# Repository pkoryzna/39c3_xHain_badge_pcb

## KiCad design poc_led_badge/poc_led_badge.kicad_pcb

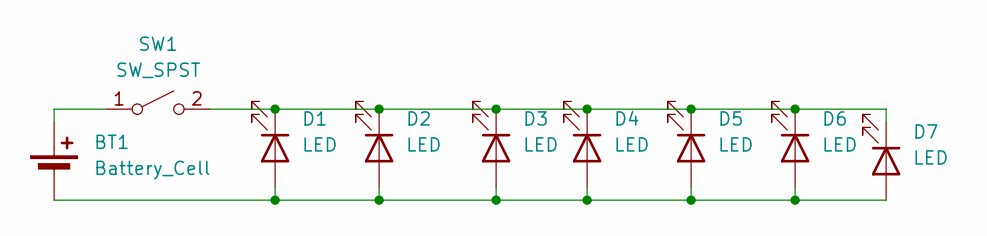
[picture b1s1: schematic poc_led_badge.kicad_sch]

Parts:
BT1: Battery_Cell; BatteryHolder_Keystone_1060_1x2032
D1, D2, D3, D4, D5, D6, D7: LED; LED_THT_SMD_Pads
SW1: SW_SPST; SW_Tactile_SPST_KAN-28

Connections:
unnamed: BT1.1 (+), SW1.1 (A)
unnamed: BT1.2 (-), D1.2 (A), D2.2 (A), D3.2 (A), D4.2 (A), D5.2 (A), D6.2 (A), D7.2 (A)
unnamed: D1.1 (K), D2.1 (K), D3.1 (K), D4.1 (K), D5.1 (K), D6.1 (K), D7.1 (K), SW1.2 (B)

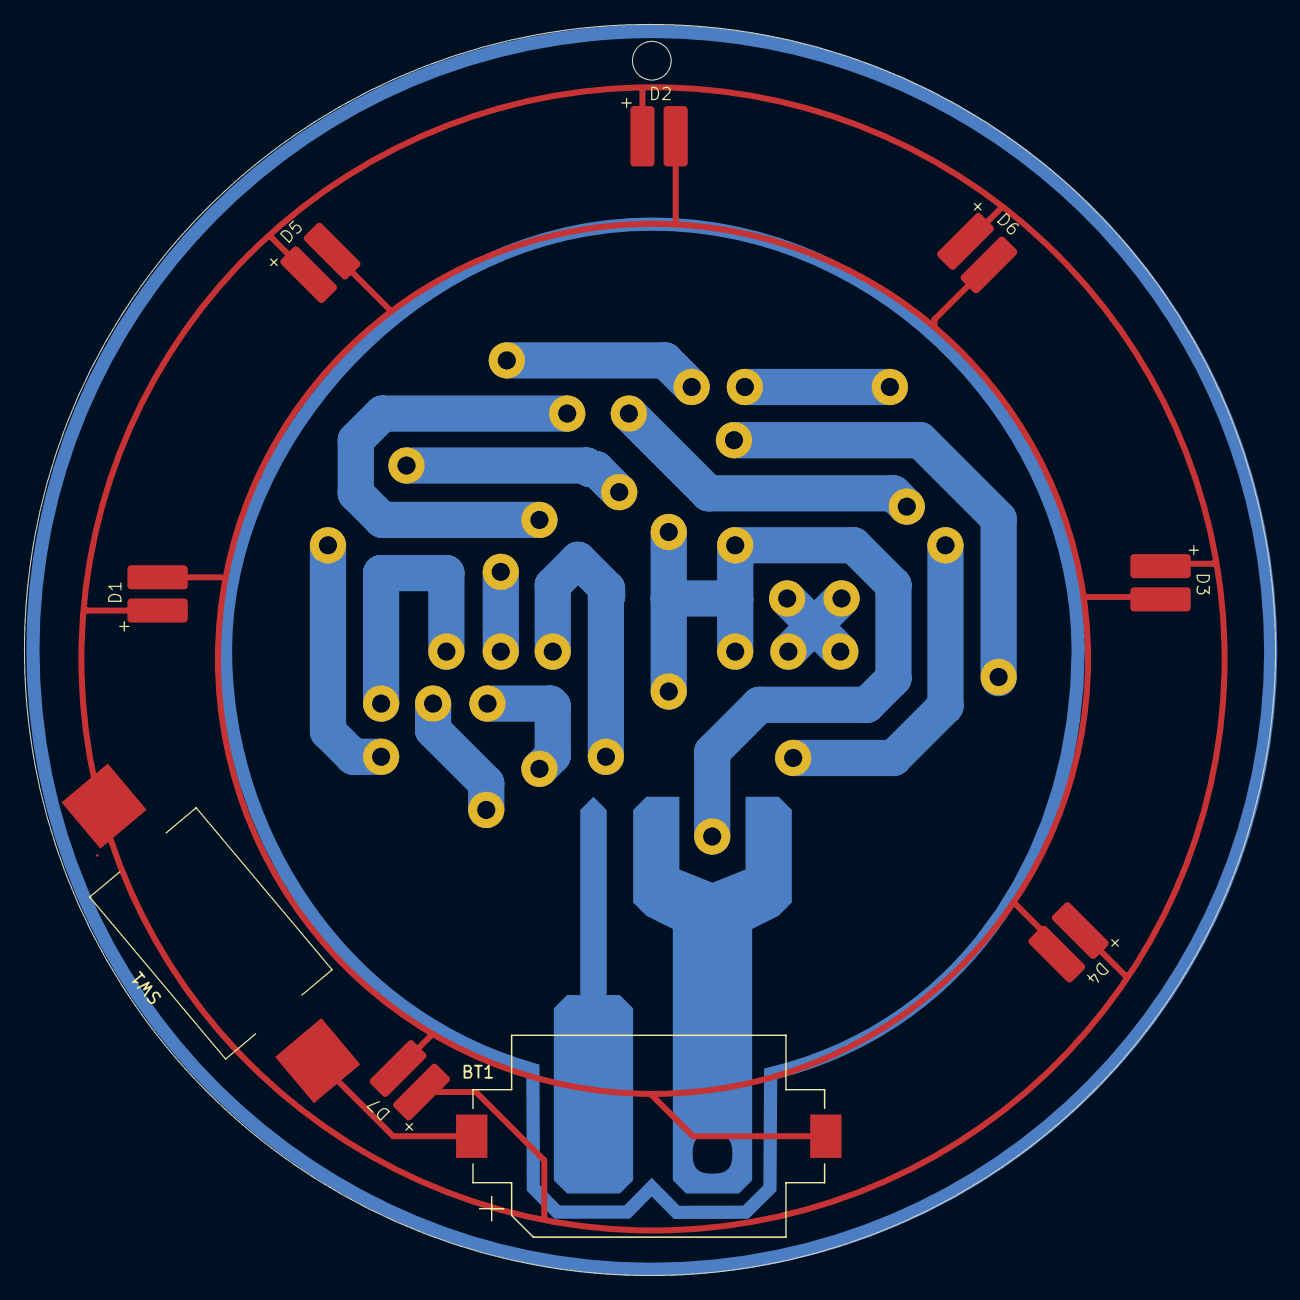
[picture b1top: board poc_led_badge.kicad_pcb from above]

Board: 2 copper layers, 103.5 x 103.5 mm, 9 parts (0 on the bottom side), 3 nets.

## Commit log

2025-11-05 update footprints
2025-11-05 thicker traces, more leds
2025-11-05 update images
2025-11-30 70 mm version
